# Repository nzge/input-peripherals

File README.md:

# Input Peripherals

An investigation into the customization potential of input devices and their core functionality.

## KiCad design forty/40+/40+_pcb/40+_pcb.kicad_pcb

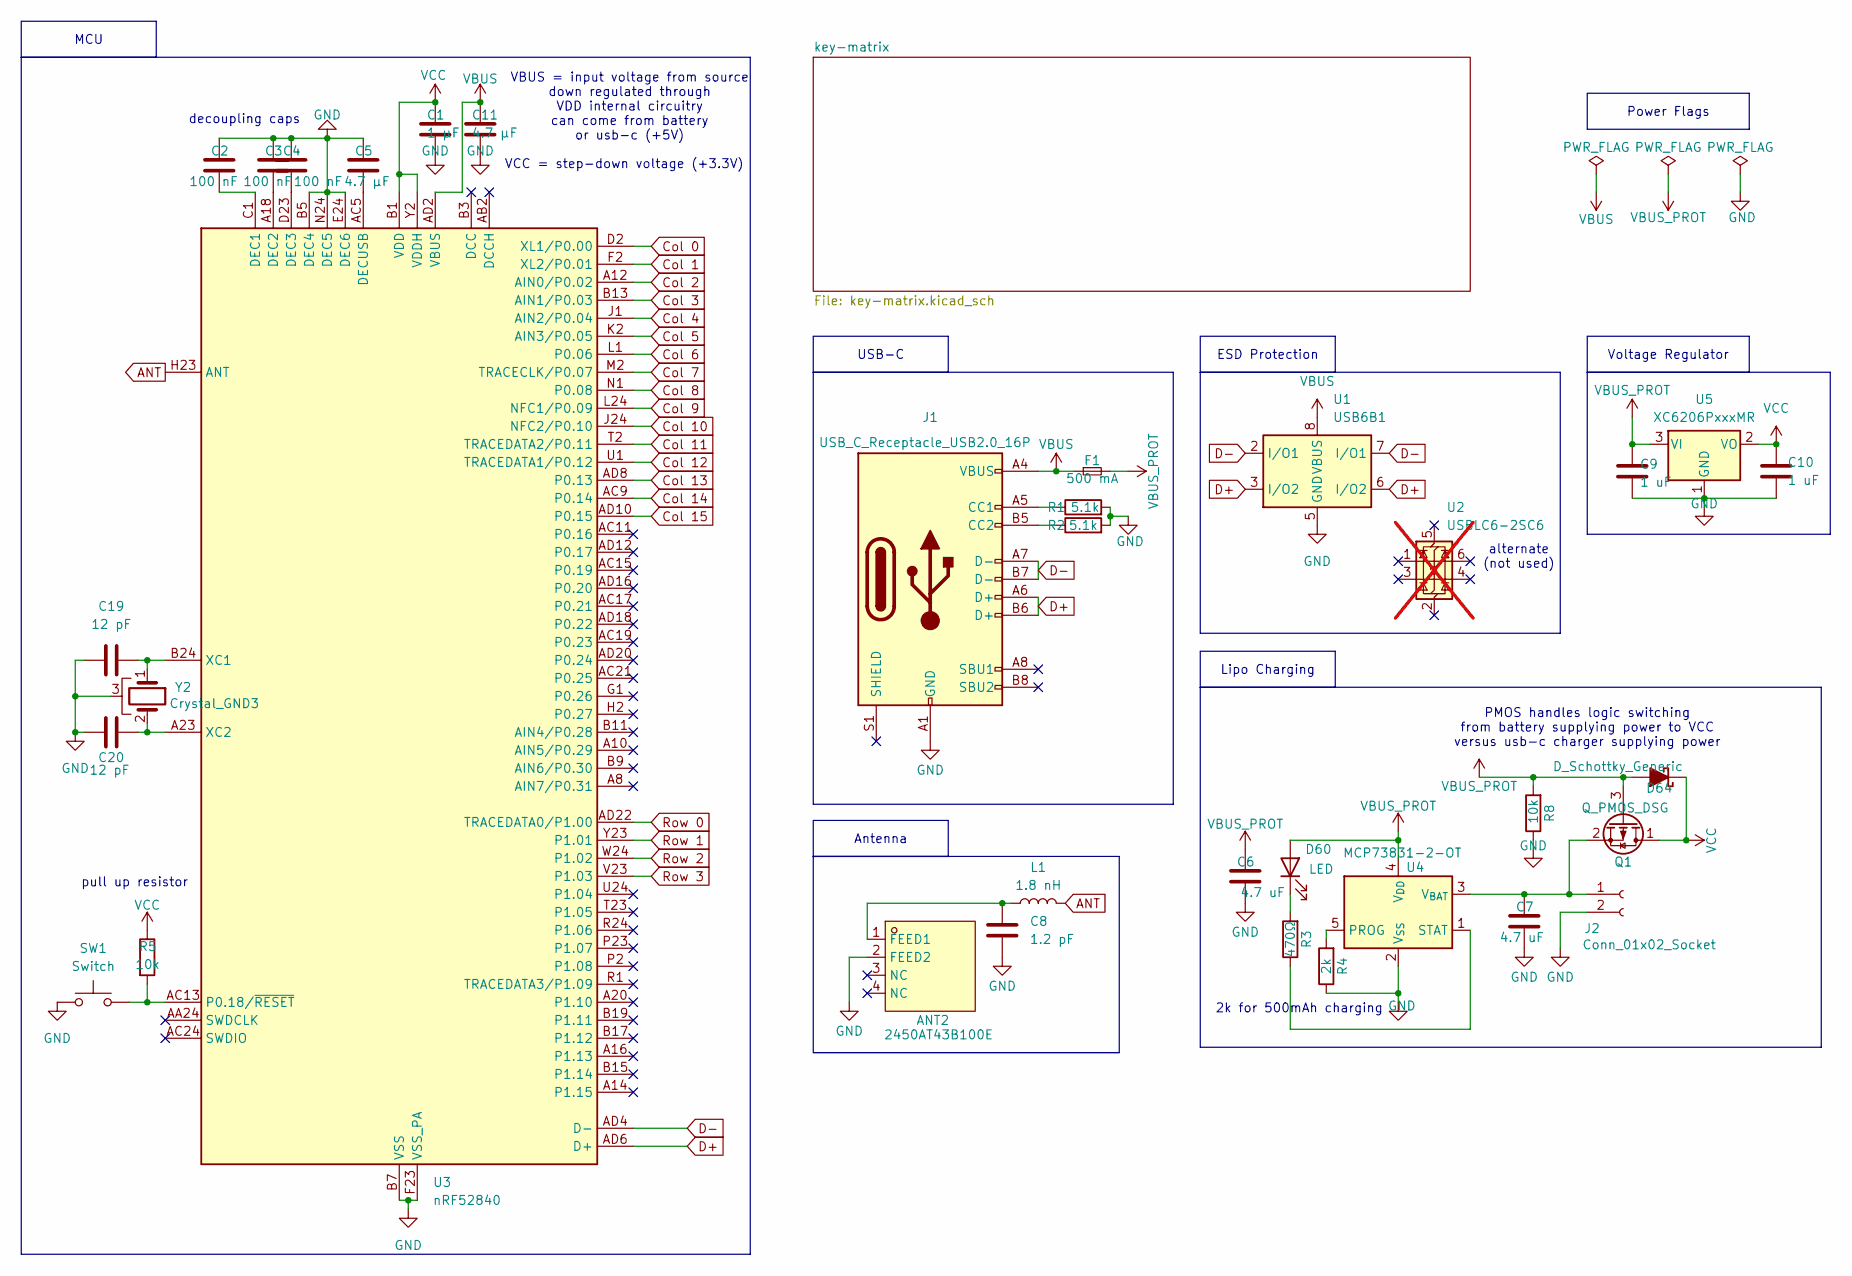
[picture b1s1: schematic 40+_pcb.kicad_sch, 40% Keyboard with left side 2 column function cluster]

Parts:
ANT2: 2450AT43B100E; ANT-SMD_4P-L7.0-W2.0-R; LCSC Part C2917721
C1: 1 µF; C_0603_1608Metric_Pad1.08x0.95mm_HandSolder
C2, C3, C4: 100 nF; C_0603_1608Metric_Pad1.08x0.95mm_HandSolder
C5, C11: 4.7 µF; C_0603_1608Metric_Pad1.08x0.95mm_HandSolder
C6, C7: 4.7 uF; C_0603_1608Metric_Pad1.08x0.95mm_HandSolder
C8: 1.2 pF; C_0402_1005Metric_Pad0.74x0.62mm_HandSolder
C9, C10: 1 uF; C_0603_1608Metric_Pad1.08x0.95mm_HandSolder
C19, C20: 12 pF; C_0402_1005Metric_Pad0.74x0.62mm_HandSolder
D60: LED; LED_0603_1608Metric_Pad1.05x0.95mm_HandSolder
D64: D_Schottky_Generic; D_2114_3652Metric_Pad1.85x3.75mm_HandSolder
F1: 500 mA; Fuse_1206_3216Metric_Pad1.42x1.75mm_HandSolder
J1: USB_C_Receptacle_USB2.0_16P; USB_C_Receptacle_HRO_TYPE-C-31-M-12
J2: Conn_01x02_Socket; JST_PH_S2B-PH-K_1x02_P2.00mm_Horizontal
L1: 1.8 nH; L_0402_1005Metric_Pad0.77x0.64mm_HandSolder
Q1: Q_PMOS_DSG; SOT-23
R1, R2: 5.1k; R_0603_1608Metric_Pad0.98x0.95mm_HandSolder
R3: 470Ω; R_0603_1608Metric_Pad0.98x0.95mm_HandSolder
R4: 2k; R_0603_1608Metric_Pad0.98x0.95mm_HandSolder
R5, R8: 10k; R_0603_1608Metric_Pad0.98x0.95mm_HandSolder
SW1: Switch; SW_SPST_TL3342
U1: USB6B1; SOIC-8_3.9x4.9mm_P1.27mm
U2: USBLC6-2SC6; SOT-23-6; not fitted
U3: nRF52840; Nordic_AQFN-73-1EP_7x7mm_P0.5mm
U4: MCP73831-2-OT; SOT-23-5_HandSoldering
U5: XC6206PxxxMR; SOT-23-3
Y2: Crystal_GND3; Crystal_SMD_3225-4Pin_3.2x2.5mm_HandSoldering

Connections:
ANT: L1.2, U3.H23 (ANT)
Col 0: U3.D2 (XL1/P0.00); also elsewhere on the board
Col 1: U3.F2 (XL2/P0.01); also elsewhere on the board
Col 2: U3.A12 (AIN0/P0.02); also elsewhere on the board
Col 3: U3.B13 (AIN1/P0.03); also elsewhere on the board
Col 4: U3.J1 (AIN2/P0.04); also elsewhere on the board
Col 5: U3.K2 (AIN3/P0.05); also elsewhere on the board
Col 6: U3.L1 (P0.06); also elsewhere on the board
Col 7: U3.M2 (TRACECLK/P0.07); also elsewhere on the board
Col 8: U3.N1 (P0.08); also elsewhere on the board
Col 9: U3.L24 (NFC1/P0.09); also elsewhere on the board
Col 10: U3.J24 (NFC2/P0.10); also elsewhere on the board
Col 11: U3.T2 (TRACEDATA2/P0.11); also elsewhere on the board
Col 12: U3.U1 (TRACEDATA1/P0.12); also elsewhere on the board
Col 13: U3.AD8 (P0.13); also elsewhere on the board
Col 14: U3.AC9 (P0.14); also elsewhere on the board
Col 15: U3.AD10 (P0.15); also elsewhere on the board
D+: J1.A6 (D+), J1.B6 (D+), U1.3 (I/O2), U1.6 (I/O2), U3.AD6 (D+)
D-: J1.A7 (D-), J1.B7 (D-), U1.2 (I/O1), U1.7 (I/O1), U3.AD4 (D-)
GND: ANT2.2 (FEED2), C1.2, C2.1, C3.1, C4.1, C5.1, C6.2, C7.2, C8.2, C9.2, C10.2, C11.2, C19.1, C20.1, J1.A1 (GND), J1.A12 (GND), J1.B1 (GND), J1.B12 (GND), J2.2, R1.2, R2.2, R4.1, R8.1, SW1.1, U1.4 (GND), U1.5 (GND), U3.B5 (DEC4), U3.B7 (VSS), U3.E24 (DEC6), U3.EP (VSS), U3.F23 (VSS_PA), U3.N24 (DEC5), U4.2 (V_{SS}), U5.1 (GND), Y2.3
unnamed: ANT2.1 (FEED1), C8.1, L1.1
unnamed: D60.1 (K), R3.2
unnamed: J1.A5 (CC1), R1.1
unnamed: J1.B5 (CC2), R2.1
unnamed: C7.1, J2.1, Q1.2 (S), U4.3 (V_{BAT})
unnamed: C2.2, U3.C1 (DEC1)
unnamed: C3.2, U3.A18 (DEC2)
unnamed: C4.2, U3.D23 (DEC3)
unnamed: C5.2, U3.AC5 (DECUSB)
unnamed: R5.2, SW1.2, U3.AC13 (P0.18/~RESET)
unnamed: C19.2, U3.B24 (XC1), Y2.1
unnamed: C20.2, U3.A23 (XC2), Y2.2
unnamed: R4.2, U4.5 (PROG)
unnamed: R3.1, U4.1 (STAT)
Row 0: U3.AD22 (TRACEDATA0/P1.00); also elsewhere on the board
Row 1: U3.Y23 (P1.01); also elsewhere on the board
Row 2: U3.W24 (P1.02); also elsewhere on the board
Row 3: U3.V23 (P1.03); also elsewhere on the board
VBUS: C11.1, F1.1, J1.A4 (VBUS), J1.A9 (VBUS), J1.B4 (VBUS), J1.B9 (VBUS), U1.1 (VBUS), U1.8 (VBUS), U3.AD2 (VBUS)
VBUS_PROT: C6.1, C9.1, D60.2 (A), D64.2 (A), F1.2, Q1.3 (G), R8.2, U4.4 (V_{DD}), U5.3 (VI)
VCC: C1.1, C10.1, D64.1 (K), Q1.1 (D), R5.1, U3.A22 (VDD), U3.AD14 (VDD), U3.AD23 (VDD), U3.B1 (VDD), U3.W1 (VDD), U3.Y2 (VDDH), U5.2 (VO)

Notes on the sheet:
pull up resistor
decoupling caps
PMOS handles logic switching from battery supplying power to VCC versus usb-c charger supplying power
alternate (not used)
VBUS = input voltage from source down regulated through VDD internal circuitry can come from battery or usb-c (+5V)
VCC = step-down voltage (+3.3V)
2k for 500mAh charging
Power Flags
USB-C
ESD Protection
Antenna
Lipo Charging
Voltage Regulator
MCU

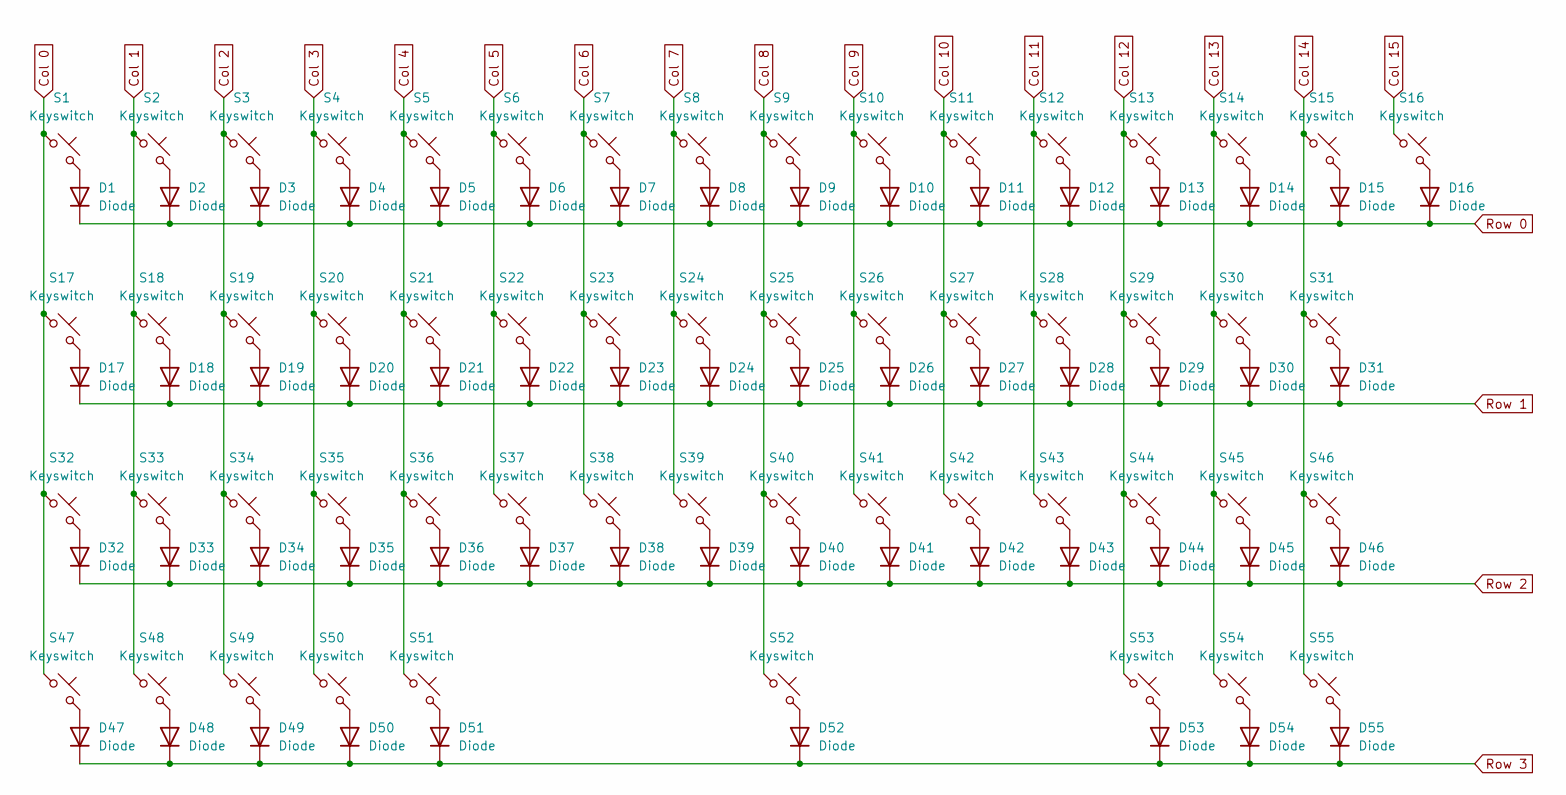
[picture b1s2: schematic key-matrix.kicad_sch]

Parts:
D1, D2, D3, D4, D5, D6, D7, D8, D9, D10, D11, D12, D13, D14, D15, D16, D17, D18, D19, D20, D21, D22, D23, D24, D25, D26, D27, D28, D29, D30, D31, D32, D33, D34, D35, D36, D37, D38, D39, D40, D41, D42, D43, D44, D45, D46, D47, D48, D49, D50, D51, D52, D53, D54, D55: Diode; D_SOD-123
S1, S2, S3, S4, S5, S6, S7, S8, S9, S10, S11, S12, S13, S14, S15, S16, S17, S18, S19, S20, S21, S22, S23, S24, S25, S26, S27, S28, S29, S30, S31, S32, S33, S34, S35, S36, S37, S38, S39, S40, S41, S42, S43, S44, S45, S46, S47, S48, S49, S50, S51, S52, S53, S54, S55: Keyswitch; MX-Alps-Hybrid-1U

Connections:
Col 0: S1.1, S17.1, S32.1, S47.1; also elsewhere on the board
Col 1: S2.1, S18.1, S33.1, S48.1; also elsewhere on the board
Col 2: S3.1, S19.1, S34.1, S49.1; also elsewhere on the board
Col 3: S4.1, S20.1, S35.1, S50.1; also elsewhere on the board
Col 4: S5.1, S21.1, S36.1, S51.1; also elsewhere on the board
Col 5: S6.1, S22.1, S37.1; also elsewhere on the board
Col 6: S7.1, S23.1, S38.1; also elsewhere on the board
Col 7: S8.1, S24.1, S39.1; also elsewhere on the board
Col 8: S9.1, S25.1, S40.1, S52.1; also elsewhere on the board
Col 9: S10.1, S26.1, S41.1; also elsewhere on the board
Col 10: S11.1, S27.1, S42.1; also elsewhere on the board
Col 11: S12.1, S28.1, S43.1; also elsewhere on the board
Col 12: S13.1, S29.1, S44.1, S53.1; also elsewhere on the board
Col 13: S14.1, S30.1, S45.1, S54.1; also elsewhere on the board
Col 14: S15.1, S31.1, S46.1, S55.1; also elsewhere on the board
Col 15: S16.1; also elsewhere on the board
unnamed: D1.2 (A), S1.2
unnamed: D2.2 (A), S2.2
unnamed: D3.2 (A), S3.2
unnamed: D4.2 (A), S4.2
unnamed: D5.2 (A), S5.2
unnamed: D6.2 (A), S6.2
unnamed: D7.2 (A), S7.2
unnamed: D8.2 (A), S8.2
unnamed: D9.2 (A), S9.2
unnamed: D10.2 (A), S10.2
unnamed: D11.2 (A), S11.2
unnamed: D12.2 (A), S12.2
unnamed: D13.2 (A), S13.2
unnamed: D14.2 (A), S14.2
unnamed: D15.2 (A), S15.2
unnamed: D16.2 (A), S16.2
unnamed: D17.2 (A), S17.2
unnamed: D18.2 (A), S18.2
unnamed: D19.2 (A), S19.2
unnamed: D20.2 (A), S20.2
unnamed: D21.2 (A), S21.2
unnamed: D22.2 (A), S22.2
unnamed: D23.2 (A), S23.2
unnamed: D24.2 (A), S24.2
unnamed: D25.2 (A), S25.2
unnamed: D26.2 (A), S26.2
unnamed: D27.2 (A), S27.2
unnamed: D28.2 (A), S28.2
unnamed: D29.2 (A), S29.2
unnamed: D30.2 (A), S30.2
unnamed: D31.2 (A), S31.2
unnamed: D32.2 (A), S32.2
unnamed: D33.2 (A), S33.2
unnamed: D34.2 (A), S34.2
unnamed: D35.2 (A), S35.2
unnamed: D36.2 (A), S36.2
unnamed: D37.2 (A), S37.2
unnamed: D38.2 (A), S38.2
unnamed: D39.2 (A), S39.2
unnamed: D40.2 (A), S40.2
unnamed: D41.2 (A), S41.2
unnamed: D42.2 (A), S42.2
unnamed: D43.2 (A), S43.2
unnamed: D44.2 (A), S44.2
unnamed: D45.2 (A), S45.2
unnamed: D46.2 (A), S46.2
unnamed: D47.2 (A), S47.2
unnamed: D48.2 (A), S48.2
unnamed: D49.2 (A), S49.2
unnamed: D50.2 (A), S50.2
unnamed: D51.2 (A), S51.2
unnamed: D52.2 (A), S52.2
unnamed: D53.2 (A), S53.2
unnamed: D54.2 (A), S54.2
unnamed: D55.2 (A), S55.2
Row 0: D1.1 (K), D2.1 (K), D3.1 (K), D4.1 (K), D5.1 (K), D6.1 (K), D7.1 (K), D8.1 (K), D9.1 (K), D10.1 (K), D11.1 (K), D12.1 (K), D13.1 (K), D14.1 (K), D15.1 (K), D16.1 (K); also elsewhere on the board
Row 1: D17.1 (K), D18.1 (K), D19.1 (K), D20.1 (K), D21.1 (K), D22.1 (K), D23.1 (K), D24.1 (K), D25.1 (K), D26.1 (K), D27.1 (K), D28.1 (K), D29.1 (K), D30.1 (K), D31.1 (K); also elsewhere on the board
Row 2: D32.1 (K), D33.1 (K), D34.1 (K), D35.1 (K), D36.1 (K), D37.1 (K), D38.1 (K), D39.1 (K), D40.1 (K), D41.1 (K), D42.1 (K), D43.1 (K), D44.1 (K), D45.1 (K), D46.1 (K); also elsewhere on the board
Row 3: D47.1 (K), D48.1 (K), D49.1 (K), D50.1 (K), D51.1 (K), D52.1 (K), D53.1 (K), D54.1 (K), D55.1 (K); also elsewhere on the board

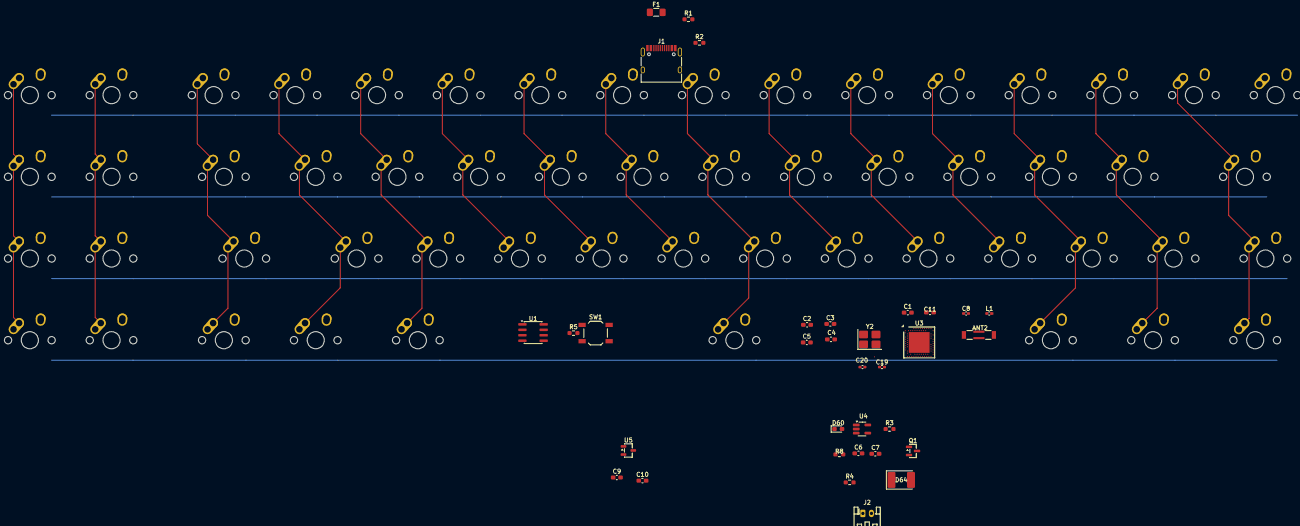
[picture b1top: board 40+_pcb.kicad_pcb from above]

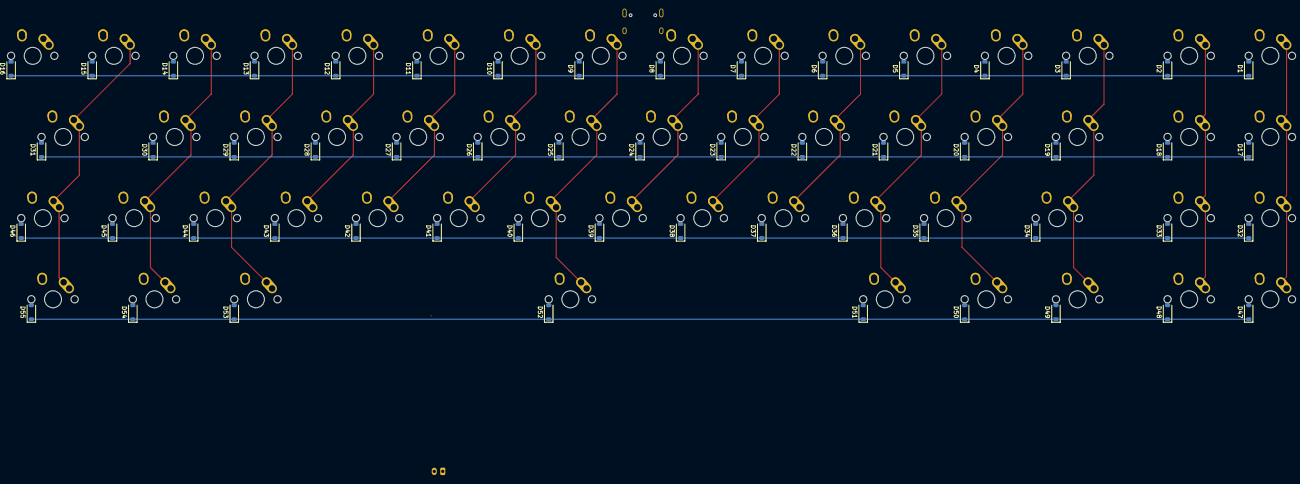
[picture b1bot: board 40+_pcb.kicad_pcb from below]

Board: 2 copper layers, 143 parts (55 on the bottom side), 96 nets.

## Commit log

2024-07-19 macropad 7-19-24 3pm
2025-03-13 11:43pm 3-12-25
2025-03-14 3:30pm 3-14-25
2025-03-14 4:02pm 3-14-25
2025-03-19 7:37pm 3-18-25
2025-03-22 5:33pm 3-21-25
2025-03-22 3:50pm 3-22-25
2025-03-25 6:41pm 3-24-25
2025-04-09 meep
2025-04-10 40% + fkeys proto
2025-04-10 pcb start
2025-04-10 Add submodules
2025-04-10 reorg
2025-04-10 submodules readd
2025-04-10 re org
2025-04-11 kicad components
2025-04-12 macro pcb
2025-04-12 firmware + qmk pcb start
2025-04-12 qmk firmware
2025-04-14 macro w/ pcb start
2025-04-16 4-14-25 11pm
2025-04-16 new categories
2025-04-28 1:31am 4-28-25
2025-04-30 4-29-25
2025-05-05 5-3-25
2025-11-04 8:16pm 11.3.25
    updating assembly relations to generate proper .glb model
2025-11-11 Add EasyEDA to KiCad symbol and 3D models
    Added EasyEDA to KiCad symbol library and associated 3D STEP/WRL models for capacitor and resistor. Updated 40+ PCB project files, removed autosave and lock files, and added a backup ZIP.
2025-11-11 Add 40%+ keyboard layout and update PCB files
    Added a new 40%+ keyboard layout JSON with function keys, updated and added KiCad PCB, schematic, and project files for the 40+ PCB, and included new backup and log files. Also added the nRF52840 spe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
